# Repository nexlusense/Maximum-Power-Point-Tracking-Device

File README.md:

# Maximum-Power-Point-Tracking-Device
Files for the Maximum Power Point Tracking (MPPT) Charge Controller Device

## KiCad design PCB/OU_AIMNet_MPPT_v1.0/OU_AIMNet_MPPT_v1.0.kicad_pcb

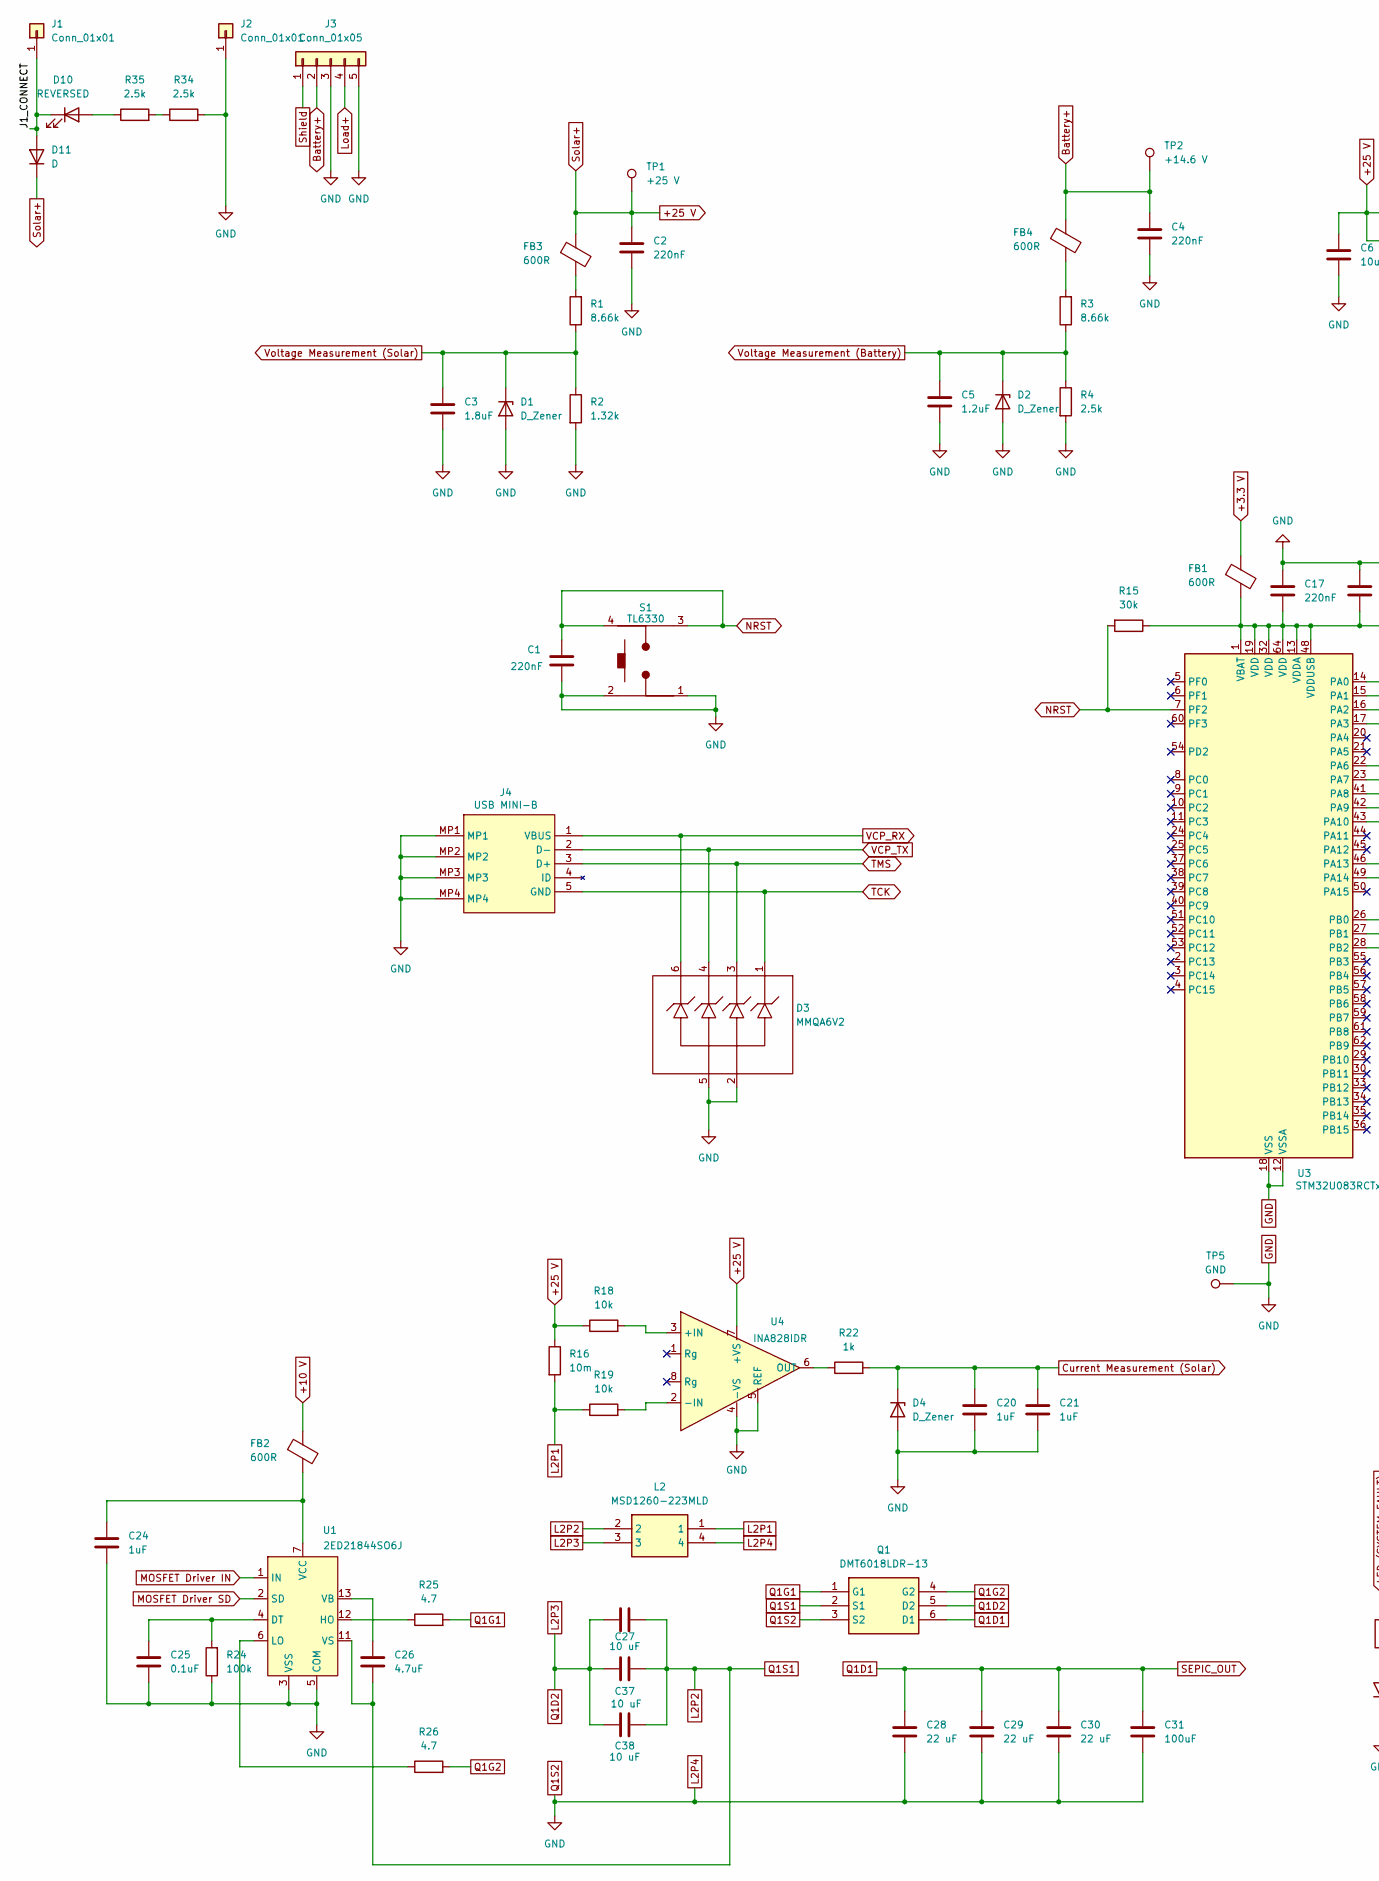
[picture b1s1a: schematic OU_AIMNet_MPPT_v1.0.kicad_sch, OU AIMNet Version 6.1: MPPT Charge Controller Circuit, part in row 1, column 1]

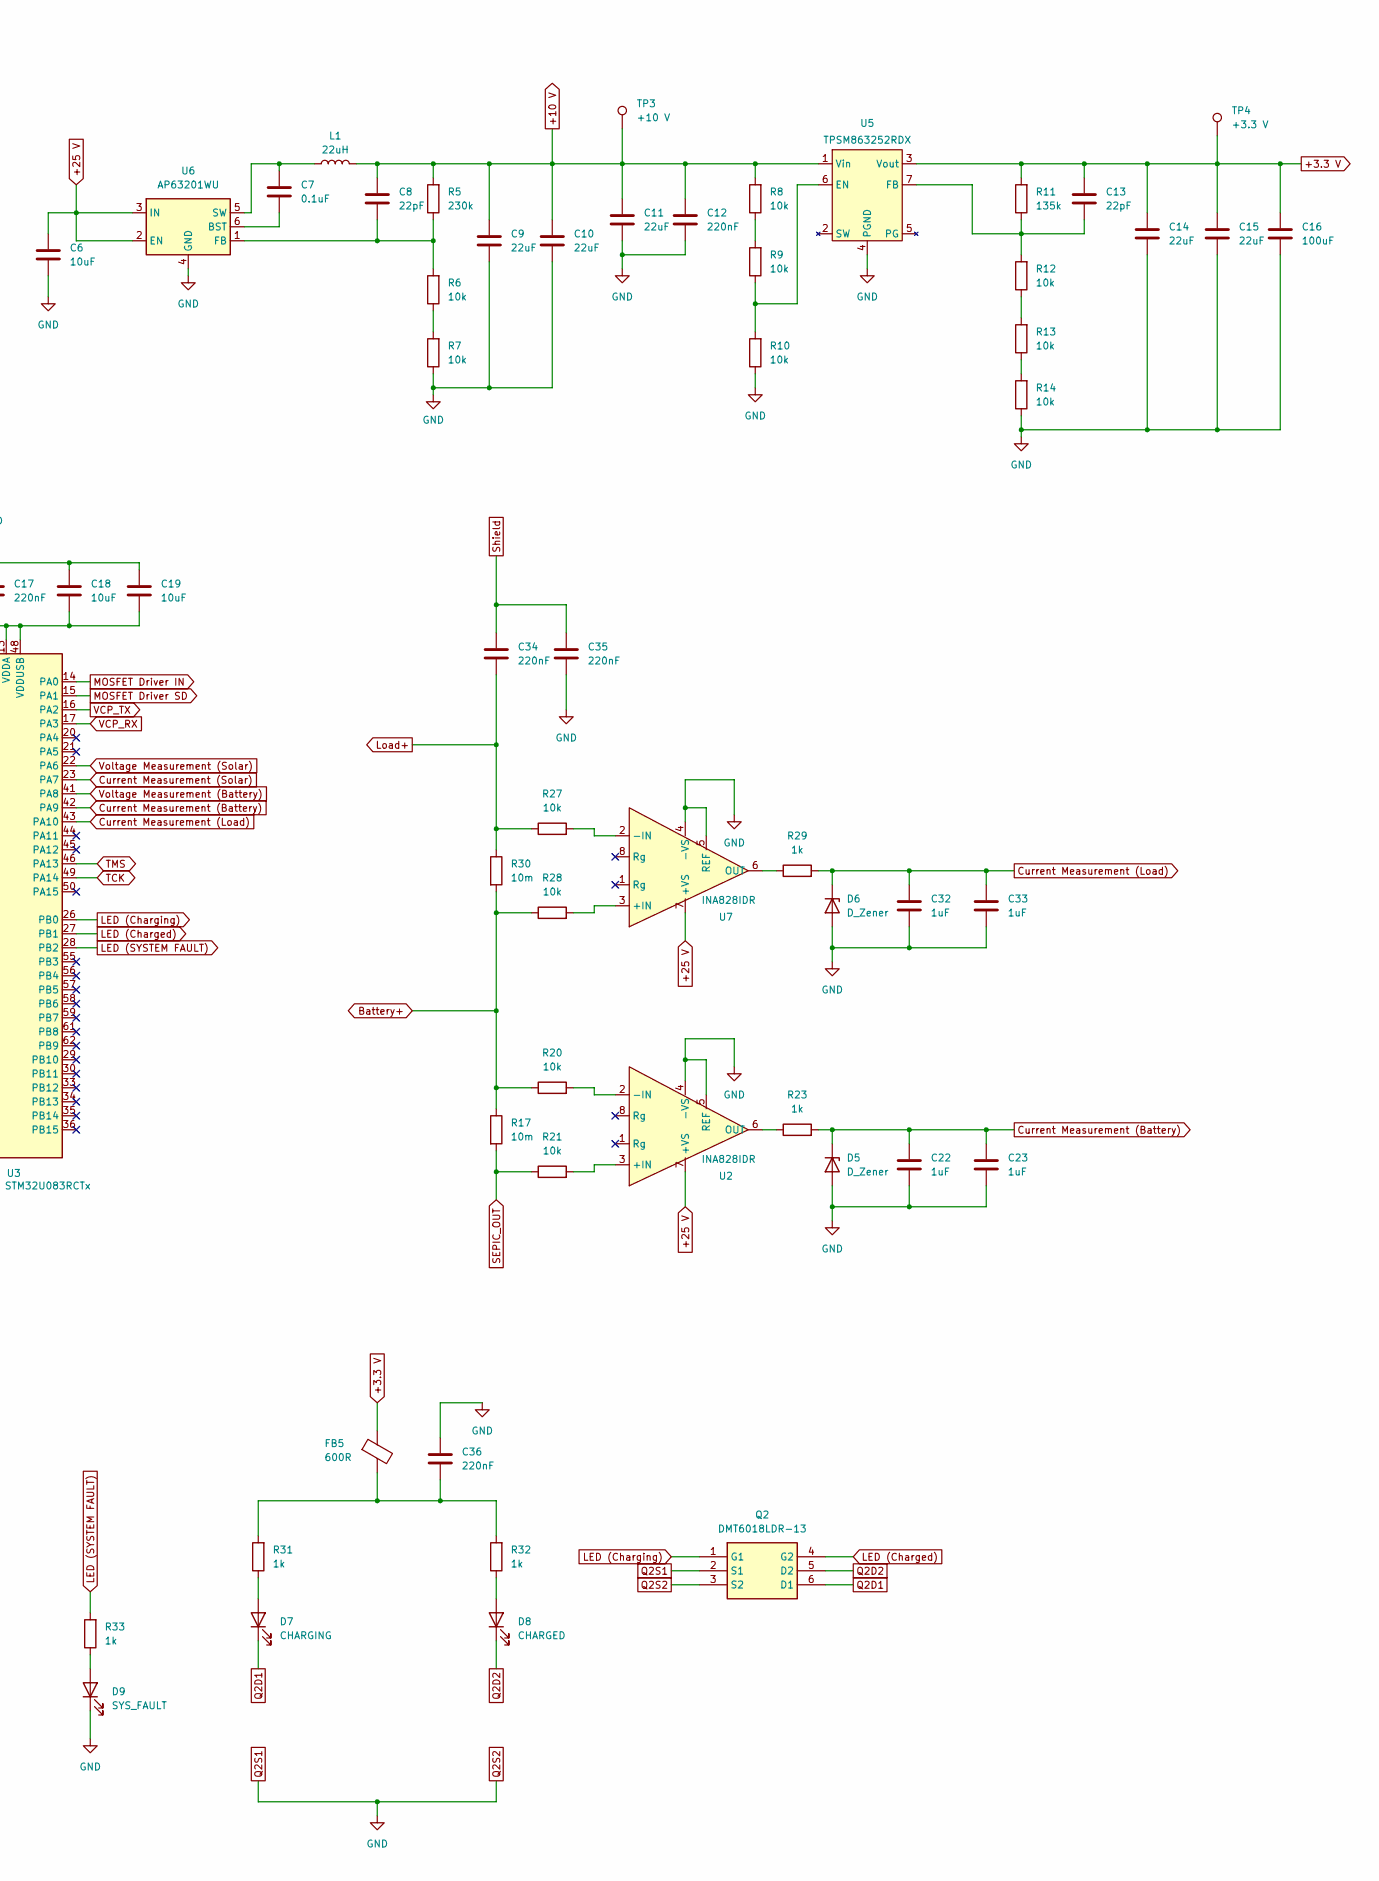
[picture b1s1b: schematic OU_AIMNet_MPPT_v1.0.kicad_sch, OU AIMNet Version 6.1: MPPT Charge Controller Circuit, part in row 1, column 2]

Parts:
C1, C2, C4, C12, C17, C34, C35, C36: 220nF; C_0805_2012Metric_Pad1.18x1.45mm_HandSolder
C3: 1.8uF; C_0805_2012Metric_Pad1.18x1.45mm_HandSolder
C5: 1.2uF; C_0805_2012Metric_Pad1.18x1.45mm_HandSolder
C6, C18, C19: 10uF; C_0805_2012Metric_Pad1.18x1.45mm_HandSolder
C7, C25: 0.1uF; C_0805_2012Metric_Pad1.18x1.45mm_HandSolder
C8, C13: 22pF; C_0805_2012Metric_Pad1.18x1.45mm_HandSolder
C9, C10, C11, C14, C15: 22uF; C_0805_2012Metric_Pad1.18x1.45mm_HandSolder
C16, C31: 100uF; C_Elec_10x10.2
C20, C21, C22, C23, C24, C32, C33: 1uF; C_0805_2012Metric_Pad1.18x1.45mm_HandSolder
C26: 4.7uF; C_0805_2012Metric_Pad1.18x1.45mm_HandSolder
C27, C37, C38: 10 uF; C_0805_2012Metric_Pad1.18x1.45mm_HandSolder
C28, C29, C30: 22 uF; C_0805_2012Metric_Pad1.18x1.45mm_HandSolder
D1, D2, D4, D5, D6: D_Zener; D_SOD-123F
D3: MMQA6V2; SOT95P280X100-6N
D7: CHARGING; LED_1206_3216Metric_Pad1.42x1.75mm_HandSolder
D8: CHARGED; LED_1206_3216Metric_Pad1.42x1.75mm_HandSolder
D9: SYS_FAULT; LED_1206_3216Metric_Pad1.42x1.75mm_HandSolder
D10: REVERSED; LED_1206_3216Metric_Pad1.42x1.75mm_HandSolder
D11: D; SMPA
FB1, FB2, FB3, FB4, FB5: 600R; L_0805_2012Metric_Pad1.05x1.20mm_HandSolder
J1, J2: Conn_01x01; PCB_Term_8191
J3: Conn_01x05; 1990038
J4: USB MINI-B; 548191572
L1: 22uH; L_Coilcraft_MSS1210-XXX
L2: MSD1260-223MLD; MSD1260T223MSB; Manufacturer_Part_Number MSD1260T-223MSB
Q1, Q2: DMT6018LDR-13; DMT6018LDR13; Manufacturer_Part_Number DMT6018LDR-13; Mouser Part Number 621-DMT6018LDR-13
R1, R3: 8.66k; R_0603_1608Metric_Pad0.98x0.95mm_HandSolder
R2: 1.32k; R_0603_1608Metric_Pad0.98x0.95mm_HandSolder
R4, R34, R35: 2.5k; R_0805_2012Metric_Pad1.20x1.40mm_HandSolder
R5: 230k; R_2512_6332Metric_Pad1.40x3.35mm_HandSolder
R6, R7, R8, R9, R10, R12, R13, R14, R18, R19, R20, R21, R27, R28: 10k; R_0402_1005Metric_Pad0.72x0.64mm_HandSolder
R11: 135k; R_0402_1005Metric_Pad0.72x0.64mm_HandSolder
R15: 30k; R_0805_2012Metric_Pad1.20x1.40mm_HandSolder
R16, R17, R30: 10m; R_2010_5025Metric_Pad1.40x2.65mm_HandSolder
R22, R23, R29, R31, R32, R33: 1k; R_0603_1608Metric_Pad0.98x0.95mm_HandSolder
R24: 100k; R_1210_3225Metric_Pad1.30x2.65mm_HandSolder
R25, R26: 4.7; R_1210_3225Metric_Pad1.30x2.65mm_HandSolder
S1: TL6330
TP1: +25 V; TestPoint_Pad_D2.0mm
TP2: +14.6 V; TestPoint_Pad_D2.0mm
TP3: +10 V; TestPoint_Pad_D2.0mm
TP4: +3.3 V; TestPoint_Pad_D2.0mm
TP5: GND; TestPoint_Pad_D2.0mm
U1: 2ED21844SO6J; SOIC127P600X172-14N
U2, U4, U7: INA828IDR; SOIC127P600X175-8N
U3: STM32U083RCTx; LQFP-64_10x10mm_P0.5mm
U5: TPSM863252RDX; TPSM863252
U6: AP63201WU; SOT95P280X100-6N

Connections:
+3.3 V: C13.1, C14.1, C15.1, C16.1, FB1.1, FB5.1, R11.2, TP4.1, U5.3 (Vout)
+10 V: C8.1, C9.1, C10.1, C11.1, C12.1, FB2.1, L1.2, R5.2, R8.2, TP3.1, U5.1 (Vin)
+25 V: C2.1, C6.1, D11.1 (K), FB3.1, R16.1, R18.1, TP1.1, U2.7 (+VS), U4.7 (+VS), U6.2 (EN), U6.3 (IN), U7.7 (+VS)
/J1_CONNECT: D10.1 (K), D11.2 (A), J1.1
Battery+: C4.1, FB4.1, J3.2, R17.1, R20.1, R28.1, R30.2, TP2.1
Current Measurement (Battery): C22.1, C23.1, D5.1 (K), R23.2, U3.42 (PA9)
Current Measurement (Load): C32.1, C33.1, D6.1 (K), R29.2, U3.43 (PA10)
Current Measurement (Solar): C20.1, C21.1, D4.1 (K), R22.2, U3.23 (PA7)
GND: C1.2, C2.2, C3.2, C4.2, C5.2, C6.2, C9.2, C10.2, C11.2, C12.2, C14.2, C15.2, C16.2, C17.1, C18.1, C19.1, C20.2, C21.2, C22.2, C23.2, C24.2, C25.2, C28.2, C29.2, C30.2, C31.2, C32.2, C33.2, C35.1, C36.1, D1.2 (A), D2.2 (A), D3.2, D3.5, D4.2 (A), D5.2 (A), D6.2 (A), D9.1 (K), J2.1, J3.3, J3.5, J4.MP1, J4.MP2, J4.MP3, J4.MP4, L2.4, Q1.3 (S2), Q2.2 (S1), Q2.3 (S2), R2.2, R4.2, R7.1, R10.1, R14.1, R24.1, R34.2, S1.1, S1.2, TP5.1, U1.3 (VSS), U1.5 (COM), U2.4 (-VS), U2.5 (REF), U3.12 (VSSA), U3.18 (VSS), U3.31 (VSS), U3.47 (VSS), U3.63 (VSS), U4.4 (-VS), U4.5 (REF), U5.4 (PGND), U6.4 (GND), U7.4 (-VS), U7.5 (REF)
L2P1: L2.1, R16.2, R19.1
L2P2: C26.2, C27.2, C37.2, C38.2, L2.2, Q1.2 (S1), U1.11 (VS)
L2P3: C27.1, C37.1, C38.1, L2.3, Q1.5 (D2)
LED (Charged): Q2.4 (G2), U3.27 (PB1)
LED (Charging): Q2.1 (G1), U3.26 (PB0)
LED (SYSTEM FAULT): R33.2, U3.28 (PB2)
Load+: C34.2, J3.4, R27.1, R30.1
MOSFET Driver IN: U1.1 (IN), U3.14 (PA0)
MOSFET Driver SD: U1.2 (SD), U3.15 (PA1)
NRST: C1.1, R15.2, S1.3, S1.4, U3.7 (PF2)
unnamed: C36.2, FB5.2, R31.2, R32.2
unnamed: D7.2 (A), R31.1
unnamed: D8.2 (A), R32.1
unnamed: D9.2 (A), R33.1
unnamed: D10.2 (A), R35.1
unnamed: FB3.2, R1.2
unnamed: FB4.2, R3.2
unnamed: R6.1, R7.2
unnamed: R8.1, R9.2
unnamed: R12.1, R13.2
unnamed: R13.1, R14.2
unnamed: R34.1, R35.2
unnamed: C25.1, R24.2, U1.4 (DT)
unnamed: R25.1, U1.12 (HO)
unnamed: R26.1, U1.6 (LO)
unnamed: C26.1, U1.13 (VB)
unnamed: C24.1, FB2.2, U1.7 (VCC)
unnamed: R21.2, U2.3 (+IN)
unnamed: R20.2, U2.2 (-IN)
unnamed: R23.1, U2.6 (OUT)
unnamed: C17.2, C18.2, C19.2, FB1.2, R15.1, U3.1 (VBAT), U3.13 (VDDA), U3.19 (VDD), U3.32 (VDD), U3.48 (VDDUSB), U3.64 (VDD)
unnamed: R18.2, U4.3 (+IN)
unnamed: R19.2, U4.2 (-IN)
unnamed: R22.1, U4.6 (OUT)
unnamed: R9.1, R10.2, U5.6 (EN)
unnamed: C13.2, R11.1, R12.2, U5.7 (FB)
unnamed: C7.2, U6.6 (BST)
unnamed: C8.2, R5.1, R6.2, U6.1 (FB)
unnamed: C7.1, L1.1, U6.5 (SW)
unnamed: R28.2, U7.3 (+IN)
unnamed: R27.2, U7.2 (-IN)
unnamed: R29.1, U7.6 (OUT)
Q1D1: C28.1, C29.1, C30.1, C31.1, Q1.6 (D1), R17.2, R21.1
Q1G1: Q1.1 (G1), R25.2
Q1G2: Q1.4 (G2), R26.2
Q2D1: D7.1 (K), Q2.6 (D1)
Q2D2: D8.1 (K), Q2.5 (D2)
Shield: C34.1, C35.2, J3.1
TCK: D3.1, J4.5 (GND), U3.49 (PA14)
TMS: D3.3, J4.3 (D+), U3.46 (PA13)
VCP_RX: D3.6, J4.1 (VBUS), U3.17 (PA3)
VCP_TX: D3.4, J4.2 (D-), U3.16 (PA2)
Voltage Measurement (Battery): C5.1, D2.1 (K), R3.1, R4.1, U3.41 (PA8)
Voltage Measurement (Solar): C3.1, D1.1 (K), R1.1, R2.1, U3.22 (PA6)

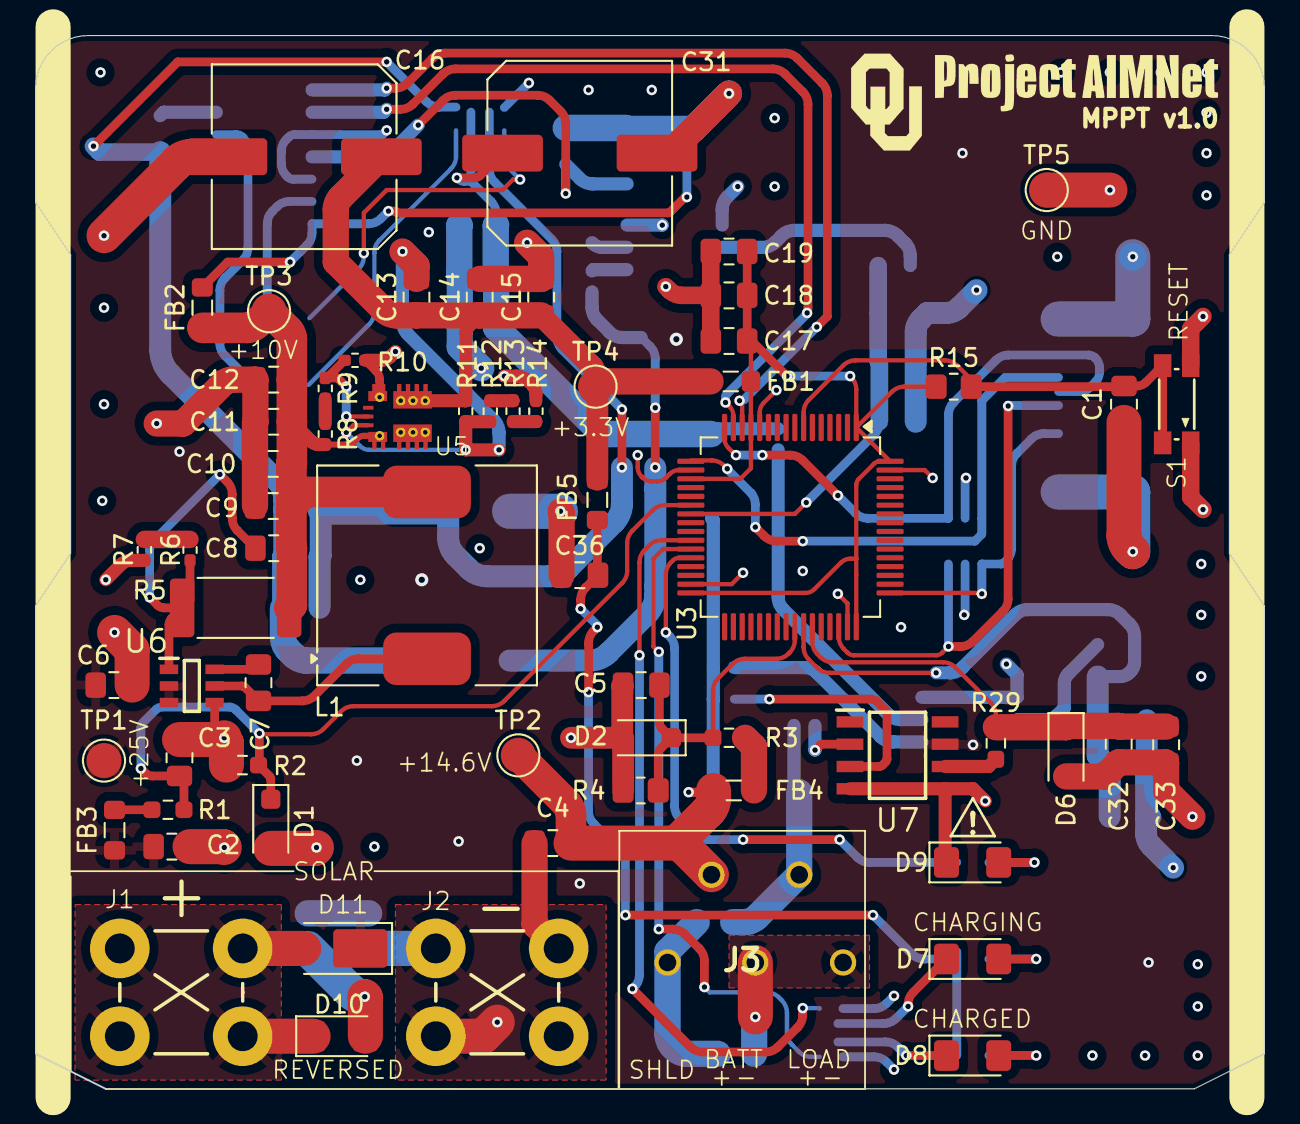
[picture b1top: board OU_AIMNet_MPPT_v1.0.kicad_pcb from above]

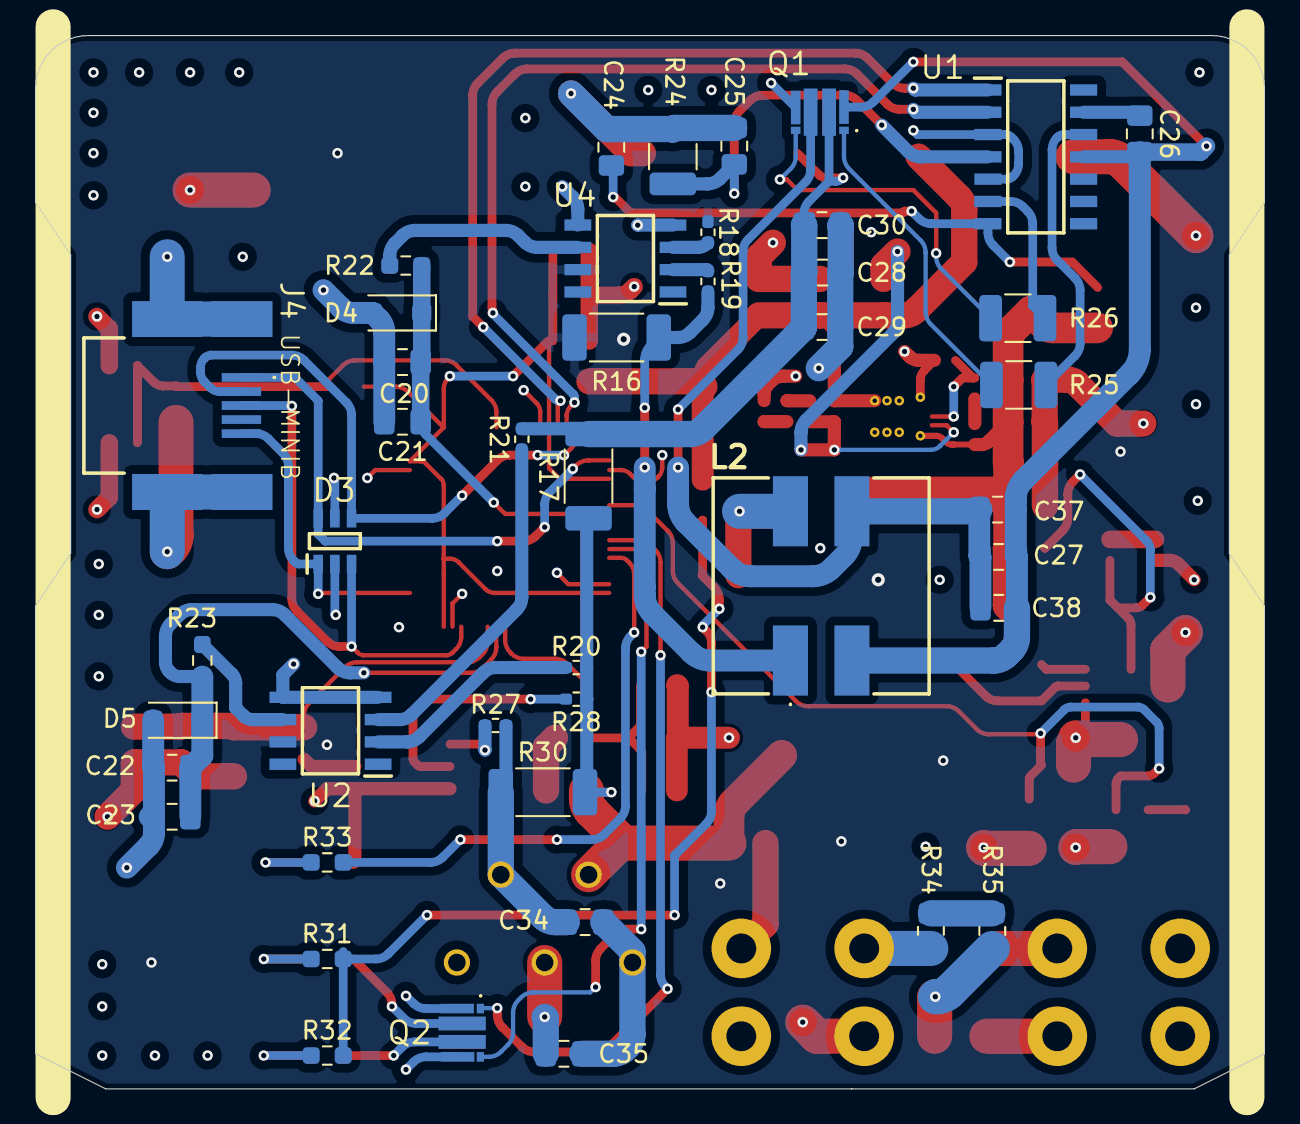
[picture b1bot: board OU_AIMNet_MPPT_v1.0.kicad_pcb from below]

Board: 4 copper layers, 70.0 x 60.0 mm, 110 parts (44 on the bottom side), 63 nets.

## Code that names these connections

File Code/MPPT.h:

#include <stdint.h>
#include "Arduino.h"

// -------------------------------------------
// STM32 Device Pinout
// -------------------------------------------

// LED Control Pins
#define LED_CHARGING PB0
#define LED_CHARGED PB1
#define LED_SYS_FAULT PB2

// Voltage and Current Sensing Pins
#define PANEL_VSENSE PA6
#define PANEL_ISENSE PA7
#define BATTERYLOAD_VSENSE PA8
#define BATTERYLOAD_ISENSE PA9
#define LOAD_ISENSE PA10

// MOSFET Gate Driver Control Pins
#define GATE_DRIVER_IN PA0 // Input PWM pin
#define GATE_DRIVER_SD PA1 // Shutdown Pin

// Analog-to-DC Converter Calibration Fields
#define VREF_INT 1.2F
#define ADC_FS_V 3.3F
#define ADC_FS_COUNT 4096.0F

// Sampling Rate of Voltage/Current Sensing
#define MPPT_SENSE_SAMPLE_RATE_MAX 2000U

// Helper Macro For Resistor Division Ratio
#define MPPTCC_RRATIO(_rt, _rb) 1.0F + (double)_rt / (double)_rb 

typedef enum
{
  MPPTCC_OK = 0x00,
  MPPTCC_BUSY = 0x01,
  MPPTCC_SYS_FAULT = 0x02
} MPPT_StatusTypeDef;

typedef struct
{
  double panel_vsense_ratio;
  double batteryload_vsense_ratio;

  uint16_t mppt_sense_sample_rate;

  double battery_vmax;
  double battery_imax;

  double curr_panel_v;
  double prev_panel_v;
  double curr_panel_i;
  double prev_panel_i;
  double curr_panel_p;
  double prev_panel_p;

  double curr_batload_v;
  double curr_batload_i;

  double curr_load_i;

  double curr_bat_i;

  uint8_t busy;
  uint8_t inhibit_charging;

  double adc_cal_value;

  uint16_t pwm_set;

} MPPT_HandleTypeDef;

void MPPTCC_Init(MPPT_HandleTypeDef *pmppt, uint16_t sample_rate, double panel_vsense_r, double batteryload_vsense_r, double vmax, double imax);
void MPPTCC_PauseCharging(MPPT_HandleTypeDef *pmppt);
void MPPTCC_ResumeCharging(MPPT_HandleTypeDef *pmppt);
MPPT_StatusTypeDef MPPTCC_GetPowerInfo(MPPT_HandleTypeDef *pmppt, double *panel_v, double *panel_i, double *bat_v, double *bat_i, double *load_v, double *load_i);
static void MPPTCC_ADCInit(MPPT_HandleTypeDef *pmppt);
static void MPPTCC_ADCCalibrate(MPPT_HandleTypeDef *pmppt);
static void MPPTCC_InterruptInit(MPPT_HandleTypeDef *pmppt);
static void MPPTCC_SenseCallbackWrapper(void);
static void MPPTCC_SenseCallback(MPPT_HandleTypeDef *pmppt);
static void MPPTCC_ControlPWM(MPPT_HandleTypeDef *pmppt);
static void MPPTCC_PWMInit(void);
static void MPPTCC_PWMWrite(uint16_t duty);
